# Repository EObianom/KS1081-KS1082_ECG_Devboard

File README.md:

# KS1081-KS1082_ECG_Devboard
Single development board that can be used for either KS1081 or KS1082 as their configuration is very similar. Any user of this repository can remove unneeded pins based on preference

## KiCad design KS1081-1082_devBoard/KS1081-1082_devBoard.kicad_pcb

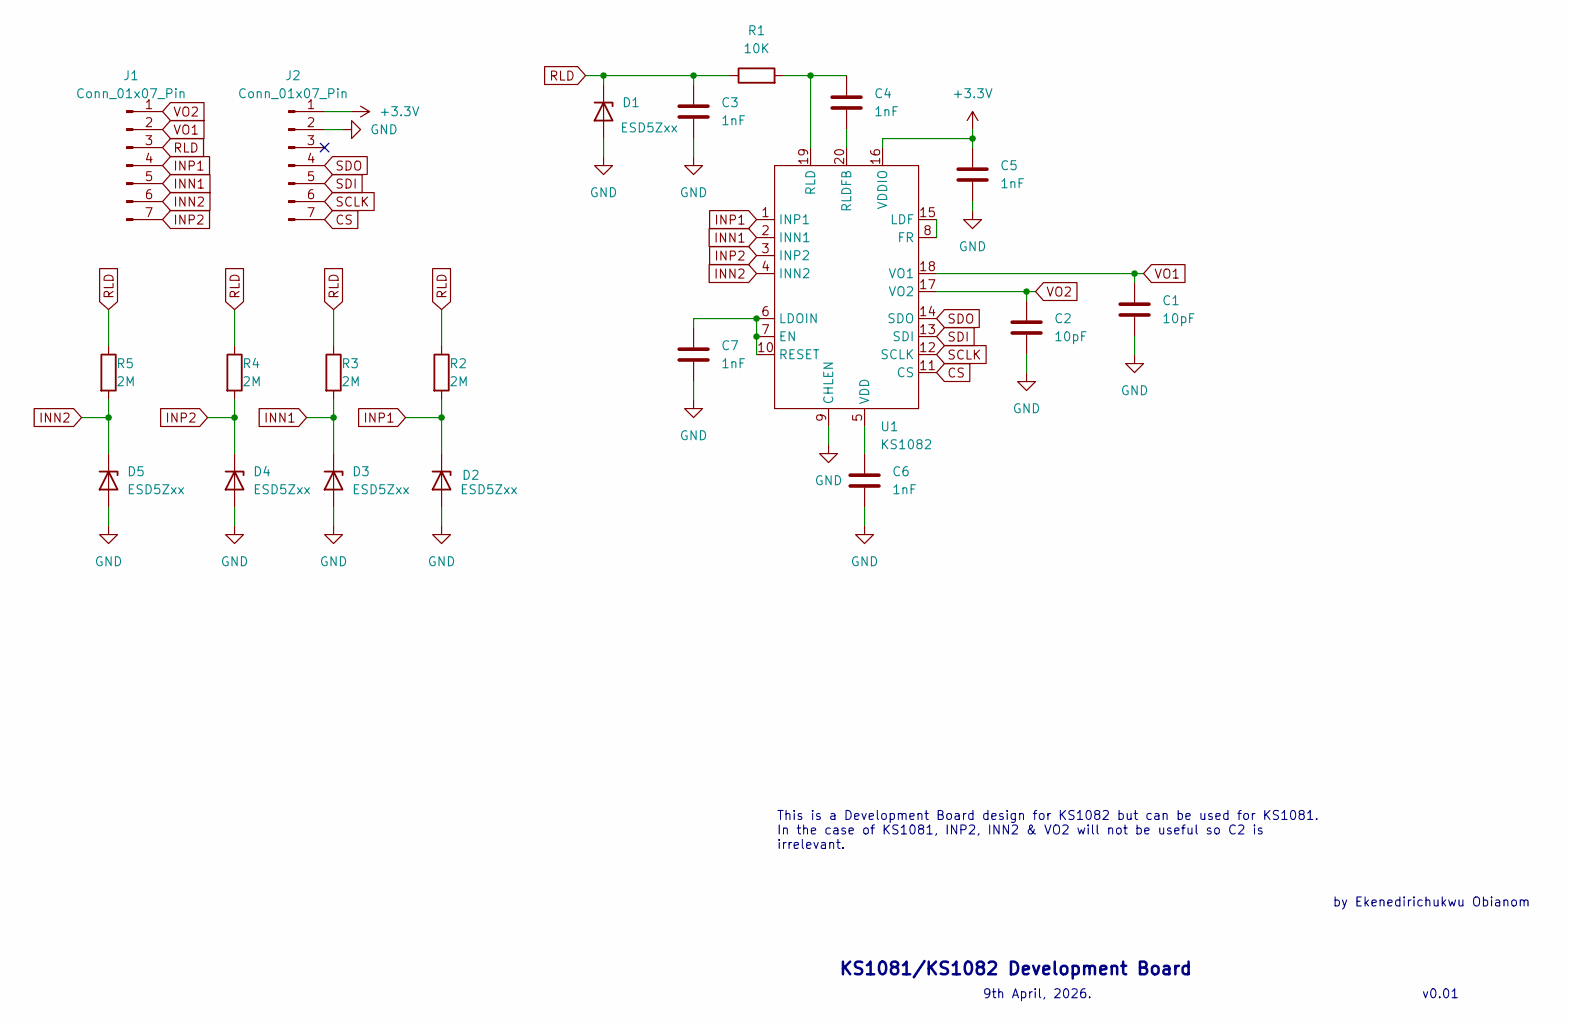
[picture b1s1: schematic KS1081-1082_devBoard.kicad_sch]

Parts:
C1, C2: 10pF; C_0603_1608Metric
C3, C4, C5, C6, C7: 1nF; C_0402_1005Metric
D1, D2, D3, D4, D5: ESD5Zxx; D_SOD-523
J1, J2: Conn_01x07_Pin; PinHeader_1x07_P2.54mm_Vertical
R1: 10K; R_0603_1608Metric
R2, R3, R4, R5: 2M; R_0603_1608Metric
U1: KS1082; QFN-20-1EP_3x3mm_P0.4mm_EP1.65x1.65mm_ThermalVias

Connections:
+3.3V: C5.1, J2.1, U1.16 (VDDIO)
CS: J2.7, U1.11 (CS)
GND: C1.2, C2.2, C3.2, C5.2, C6.2, C7.2, D1.2 (A), D2.2 (A), D3.2 (A), D4.2 (A), D5.2 (A), J2.2, U1.9 (CHLEN), U1.21 (GND)
INN1: D3.1 (K), J1.5, R3.2, U1.2 (INN1)
INN2: D5.1 (K), J1.6, R5.2, U1.4 (INN2)
INP1: D2.1 (K), J1.4, R2.2, U1.1 (INP1)
INP2: D4.1 (K), J1.7, R4.2, U1.3 (INP2)
unnamed: C7.1, U1.6 (LDOIN), U1.7 (EN), U1.10 (RESET)
unnamed: U1.8 (FR), U1.15 (LDF)
unnamed: C4.1, R1.2, U1.19 (RLD)
unnamed: C4.2, U1.20 (RLDFB)
unnamed: C6.1, U1.5 (VDD)
RLD: C3.1, D1.1 (K), J1.3, R1.1, R2.1, R3.1, R4.1, R5.1
SCLK: J2.6, U1.12 (SCLK)
SDI: J2.5, U1.13 (SDI)
SDO: J2.4, U1.14 (SDO)
VO1: C1.1, J1.2, U1.18 (VO1)
VO2: C2.1, J1.1, U1.17 (VO2)

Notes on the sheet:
This is a Development Board design for KS1082 but can be used for KS1081. In the case of KS1081, INP2, INN2 & VO2 will not be useful so C2 is irrelevant.
by Ekenedirichukwu Obianom
v0.01
KS1081/KS1082 Development Board
9th April, 2026.

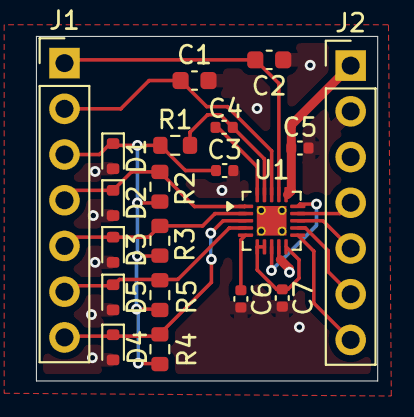
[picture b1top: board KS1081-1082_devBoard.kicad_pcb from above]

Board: 4 copper layers, 19.0 x 19.1 mm, 20 parts (0 on the bottom side), 18 nets.

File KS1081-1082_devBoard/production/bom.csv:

Designator,Footprint,Quantity,Value,LCSC Part #
"C1, C2",0603,2,10pF,
"C3, C4, C5, C6, C7",0402,5,1nF,
"D1, D2, D3, D4, D5",D_SOD-523,5,ESD5Zxx,
"J1, J2",PinHeader_1x07_P2.54mm_Vertical,2,Conn_01x07_Pin,
R1,0603,1,10K,
"R2, R3, R4, R5",0603,4,2M,
U1,QFN-20-1EP_3x3mm_P0.4mm_EP1.65x1.65mm_ThermalVias,1,KS1082,

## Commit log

2026-04-09 Add image to README for KS1081-KS1082 ECG Devboard
2026-04-09 Add KS1081-1082 dev board KiCad files
    Initial import of the KS1081-1082 development board KiCad project. Adds PCB (.kicad_pcb), schematic (.kicad_sch), project file (.kicad_pro), fabrication-toolkit options, production artifacts (zip/bac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
2026-04-09 Add production CSVs and update .gitignore
    Add BOM, designators, and pick-and-place positions for KS1081-1082_devBoard under production/ (bom.csv, designators.csv, positions.csv). These files include the component list (U1 KS1082, resistors, 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
2026-04-09 Add Creative Commons license
    Added the Creative Commons Attribution-NonCommercial-NoDerivatives 4.0 International Public License to the project.
